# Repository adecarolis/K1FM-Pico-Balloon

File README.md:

# K1FM Pico Balloon

## Introduction:

This tracker board is WSPR based and transmits on 20 meters. Version 1.3 weights 2.84 grams and takes around 55mA at 3.3V. Unlike other designs, this one includes a passband filter that significantly smooths the resulting waveforms (such filter would be legally mandatory in the United States). The board includes a power regulator and a low voltage dropout diode that can be useful if using batteries.

A maiden flight, powered by 6 39x19mm Aoshike solar panels, was attempted in New Jersey at the end of September 2019. After 5 days of transmissios the payload failed somewhere around Belize (central America) probably after encountering a tropical storm.

The recommended software is [GeminiWSPR](https://github.com/adecarolis/GeminiWspr)

Feel free to test these boards. You can purchase the latest revision (1.3) at OSHPark:

https://oshpark.com/shared_projects/ud3vH8MF

Suggestions and technical advice are welcome!

73 de Alain K1FM

## Assembly:

This is the recommended assemply sequence. Test each step individually. Do not proceed furter in case you enconter a problem in the current step.

- Install U1, C2, C3, C12, J2, Y1, R1, R2, R5 (Microcontroller)
- Use a USBasp programmer to load the Arduino bootloader (Atmel328p, 8MHz) via the ICSP port. Verify the bootloader can be uploaded without errors.
- Disconnect the USBasp from the J2 port. Connect a serial Arduino programmer to J3 (use 3V and GND connections from J2). Load the GeminiWSPR firmware (don't forget to set your own callsign and gridsquare!). Verify debug output can be seen on the serial monitor.
- Install GPS1, R6, Q2, C10 (GPS)
- Connect the GPS antenna
- In the Arduino serial monitor, verify the GPS is working
- Install Q1, U2, C11, C13, C14, R3, R4, R8, Q3 (Transmitter)
- Install L1, L2, L3, C5, C6, C7, C8, C9 (Bandpass filter)
- Connect the HF antenna 
- Verify the unit transmits WSPR on 14.0956 MHz
- Install U3, C1, C4, D1 (Power Supply)
Note: this is not needed if your power source is externally regulated or never exceeds 3.5 Volts
- Disconnect all J3/J2 connections. Verify the unit can be normally powered via J4

## Changelog:

**Version 1.0**
Initial, not functioning prototype.

**Version 1.1**
- Bugfixes

**Version 1.2**
- Added optional K1FM Pico Power board for battery charge management
- Added bottom hook for dipole antennas
- Replaced Si5351a quartz with TCXO (Q1)
- Added switches to power the Si5351a, GPS down (Q2 - Q3)
- Added temperature sensor (TMP-36)
- Added fixed V_BCK connection to 3.3V
- Added VDD measurement point (ADC0)

**Version 1.3**
- Switched to 4 Layers design
- Added Time Pulse feedback to external interrupt input (PD2)
- Added Clock Generator Feedback to T1 input (PD5)
- Added external SDA, SCL pins
- Added extra power pin for direct battery charging via Schottky diode
- Reorganized external pins, added standard ISCP header
- 4.7 voltage divider on ADC0
- Fixed Q2-Q3 Mosfet polarization
- Expanded gap between main board and "Remove Before Flight" section

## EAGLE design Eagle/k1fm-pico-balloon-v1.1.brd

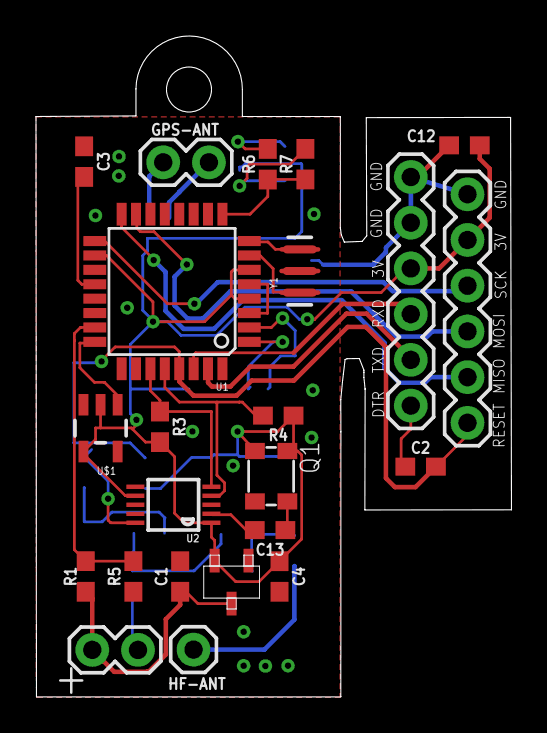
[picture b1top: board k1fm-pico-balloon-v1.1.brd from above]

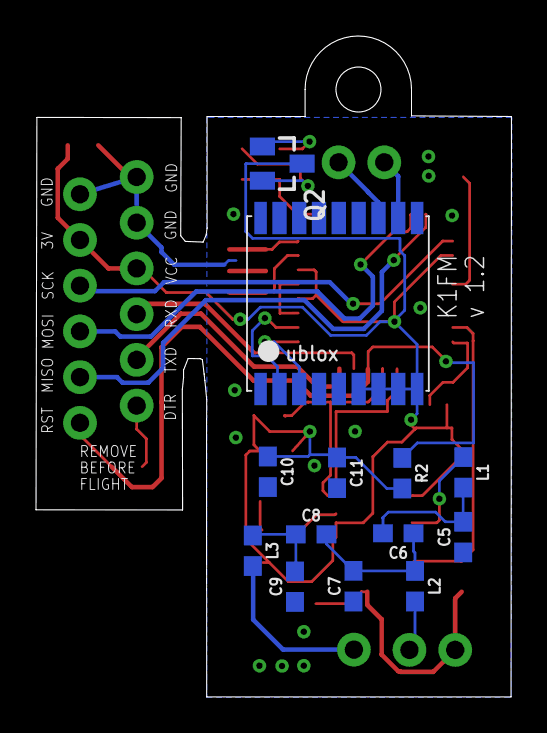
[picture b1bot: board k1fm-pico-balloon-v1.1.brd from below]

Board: 2 copper layers, 26.4 x 36.7 mm, 36 parts (13 on the bottom side), 30 nets.

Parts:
3.3V: 3.3V; 1X02
C1, C4, C12: 1.0uF; 0603
C2, C3: 0.1uF; 0603
C5, C9: 56pF; 0603
C6, C8: 18pF; 0603
C7: 47pF; 0603
C10, C11: 0.47uF; 0603
C13: 10nF; 0603
GPS1: UBLOX_MAX
GPS-ANT: GPS ANT; 1X02
HF-ANT: HF ANT; 1X01
J2, J3: 1X06
L1, L2, L3: 1.5uH; 0603
Q1: ASTX-H11-25.000MHZ-T; 3.2X2.5_KXO-84
Q2: DMP2305U; SOT23
R1, R2, R5, R7: 10k; 0603
R3, R4: 4.7k; 0603
R6: 150; 0603
U1: ATMEGA328; TQFP32-08
U2: Si5351A-B-GT; MSOP10
U3: MCP1754X-XXXXX/C; SOT-23A_MC
U$1: TMP36; SOT-23
Y1: 8/16/20MHz; RESONATOR-SMD-1:1

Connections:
3V: C4.1, C10.1, C11.1, C12.1, GPS1.6_V_BCKP, GPS1.7_VCC_IO, GPS1.8_VCC, GPS1.9_V_RESET, J2.4, J3.2, Q1.1, Q1.4, Q2.3, R2.2, R3.2, R4.1, U1.4, U1.6, U1.18, U2.1, U2.7, U3.2, U$1.2, U$1.4
ANT: HF-ANT.1, L3.2
AREF: C3.2, U1.20
CLK0: L1.1, U2.10
D3: GPS1.3_RXD1, U1.1
D4: GPS1.2_TXD1, U1.2
DTR: C2.1, J2.1
GND: 3.3V.2, C1.2, C3.1, C4.2, C5.1, C7.1, C9.1, C10.2, C11.2, C12.2, GPS1.1_GND, GPS1.10_GND, GPS1.12_GND, GPS1.15_RESERVED, GPS-ANT.1, J2.5, J2.6, J3.1, L2.2, Q1.2, R5.1, U1.3, U1.5, U1.21, U2.8, U3.1, U$1.5, Y1.2
GPS_E: R6.1, R7.1, U1.9
MISO: J3.5, U1.16
MOSI: J3.4, U1.15
unnamed: C13.1, Q1.3
unnamed: C13.2, U2.2
unnamed: Q2.2, R7.2
unnamed: R1.2, R5.2, U1.23
unnamed: Q2.1, R6.2
unnamed: GPS1.11_RF_IN, GPS-ANT.2
unnamed: C6.1, C7.2, C8.2, L2.1
unnamed: C5.2, C6.2, L1.2
unnamed: C8.1, C9.2, L3.1
unnamed: U1.8, Y1.3
unnamed: U1.7, Y1.1
RESET: C2.2, J3.6, R2.1, U1.29
RXI: J2.3, U1.30
SCK: J3.3, U1.17
SCL: R4.2, U1.28, U2.4
SDA: R3.1, U1.27, U2.5
TEMP: U1.24, U$1.1
TXO: J2.2, U1.31
VDD: 3.3V.1, C1.1, R1.1, U3.3

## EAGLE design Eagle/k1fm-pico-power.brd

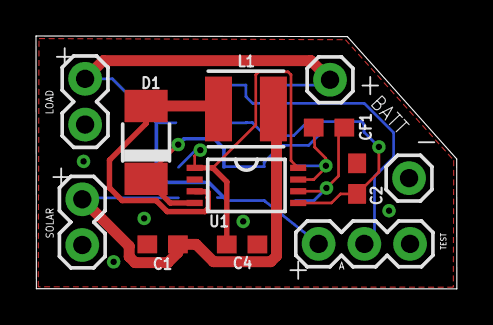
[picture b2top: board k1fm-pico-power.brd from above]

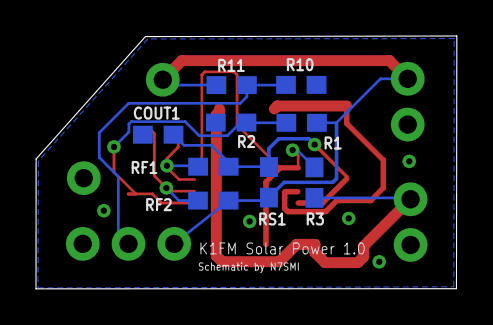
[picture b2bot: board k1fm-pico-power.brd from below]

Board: 4 copper layers, 23.4 x 14.0 mm, 21 parts (9 on the bottom side), 10 nets.

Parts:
C1: 2.2uF; 0603
C2, C4: 1uF; 0603
CF1: 1uF; 0603
COUT1: 10uF; 0603
D1: SS14; DO-214AC
J1: SOLAR; 1X02
J2: BATT +; 1X01
J3: BATT -; 1X01
J4: LOAD; 1X02
J5: TEST; 1X03
L1: 74404043220A; WE-LQS_4025
R1: 390k; 0603
R2: 130k; 0603
R3: 1k; 0603
R10, R11: 10k; 0603
RF1, RF2: 1k; 0603
RS1: 0; 0603
U1: SPV1040; TSSOP-8

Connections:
GND: C1.2, C2.2, C4.2, COUT1.1, J1.2, J3.1, J4.2, J5.3, R2.1, R10.1, U1.2
unnamed: D1.A, L1.2, U1.3
unnamed: C1.1, J1.1, L1.1, R3.2
unnamed: C4.1, R3.1, U1.1, U1.8
unnamed: J2.1, J4.1, J5.1, R1.2, R11.2, RF2.1, RS1.2
unnamed: J5.2, R10.2, R11.1
unnamed: CF1.1, RF1.2, U1.7
unnamed: C2.1, R1.1, R2.2, U1.5
unnamed: COUT1.2, D1.C, RF1.1, RS1.1, U1.4
unnamed: CF1.2, RF2.2, U1.6

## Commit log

2019-05-15 Add Eagle schmatics and boards
2019-05-15 Add PDF - Readme
2019-05-15 Add partlists
2019-05-25 4 Layers. Added external SCL, SDA, GPS lines.
2019-05-25 Removed pdf, added gitignore
2019-05-25 Reorganized TX/RX lines - Conn layout
2019-05-25 Add lck files to gitignore
2019-05-25 Refresh pdf's
2019-05-25 Add diode and connection for direct solar power
2019-05-25 Move board label
2019-05-26 Revert to classic hw/sw serial configuration
2019-05-26 Redraw VDD measure input
2019-05-27 Use diode BAT20J, space out break lines, bugfix
2019-05-29 Use PD2 (ext int) and PD5 (T1) for calibration
2019-05-29 Update parts list
2019-06-08 Fix Mosfet polarization
2019-06-08 Expand gap
2019-06-08 Refresh PDFs
2019-06-09 Fixed R1-R5 voltage divider, fixed PCB warnings
2019-06-09 Move Pico Power to separate directory
2019-06-09 Move k1fm-pico-balloon.sch
2019-06-09 Fix schematic name
2019-06-09 Rename files
2019-06-09 Update Readme, Partlist
2019-06-09 Remove wire stubs
2019-06-09 Add v1.1, fix PDFs
2019-06-09 Add v1.0
2019-06-09 Move PDFs
2019-09-28 Remove pico power
2019-09-28 Remove pico power PDF
2019-10-16 Fix Readme
2019-10-25 Remove Aries HAB reference

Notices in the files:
parts and their libraries:
SparkFun-Capacitors: Licensing: Creative Commons ShareAlike 4.0 International - https://creativecommons.org/licenses/by-sa/4.0
microbuilder: This work is placed in the public domain, and may be freely used for commercial and non-commercial work with the following conditions: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
